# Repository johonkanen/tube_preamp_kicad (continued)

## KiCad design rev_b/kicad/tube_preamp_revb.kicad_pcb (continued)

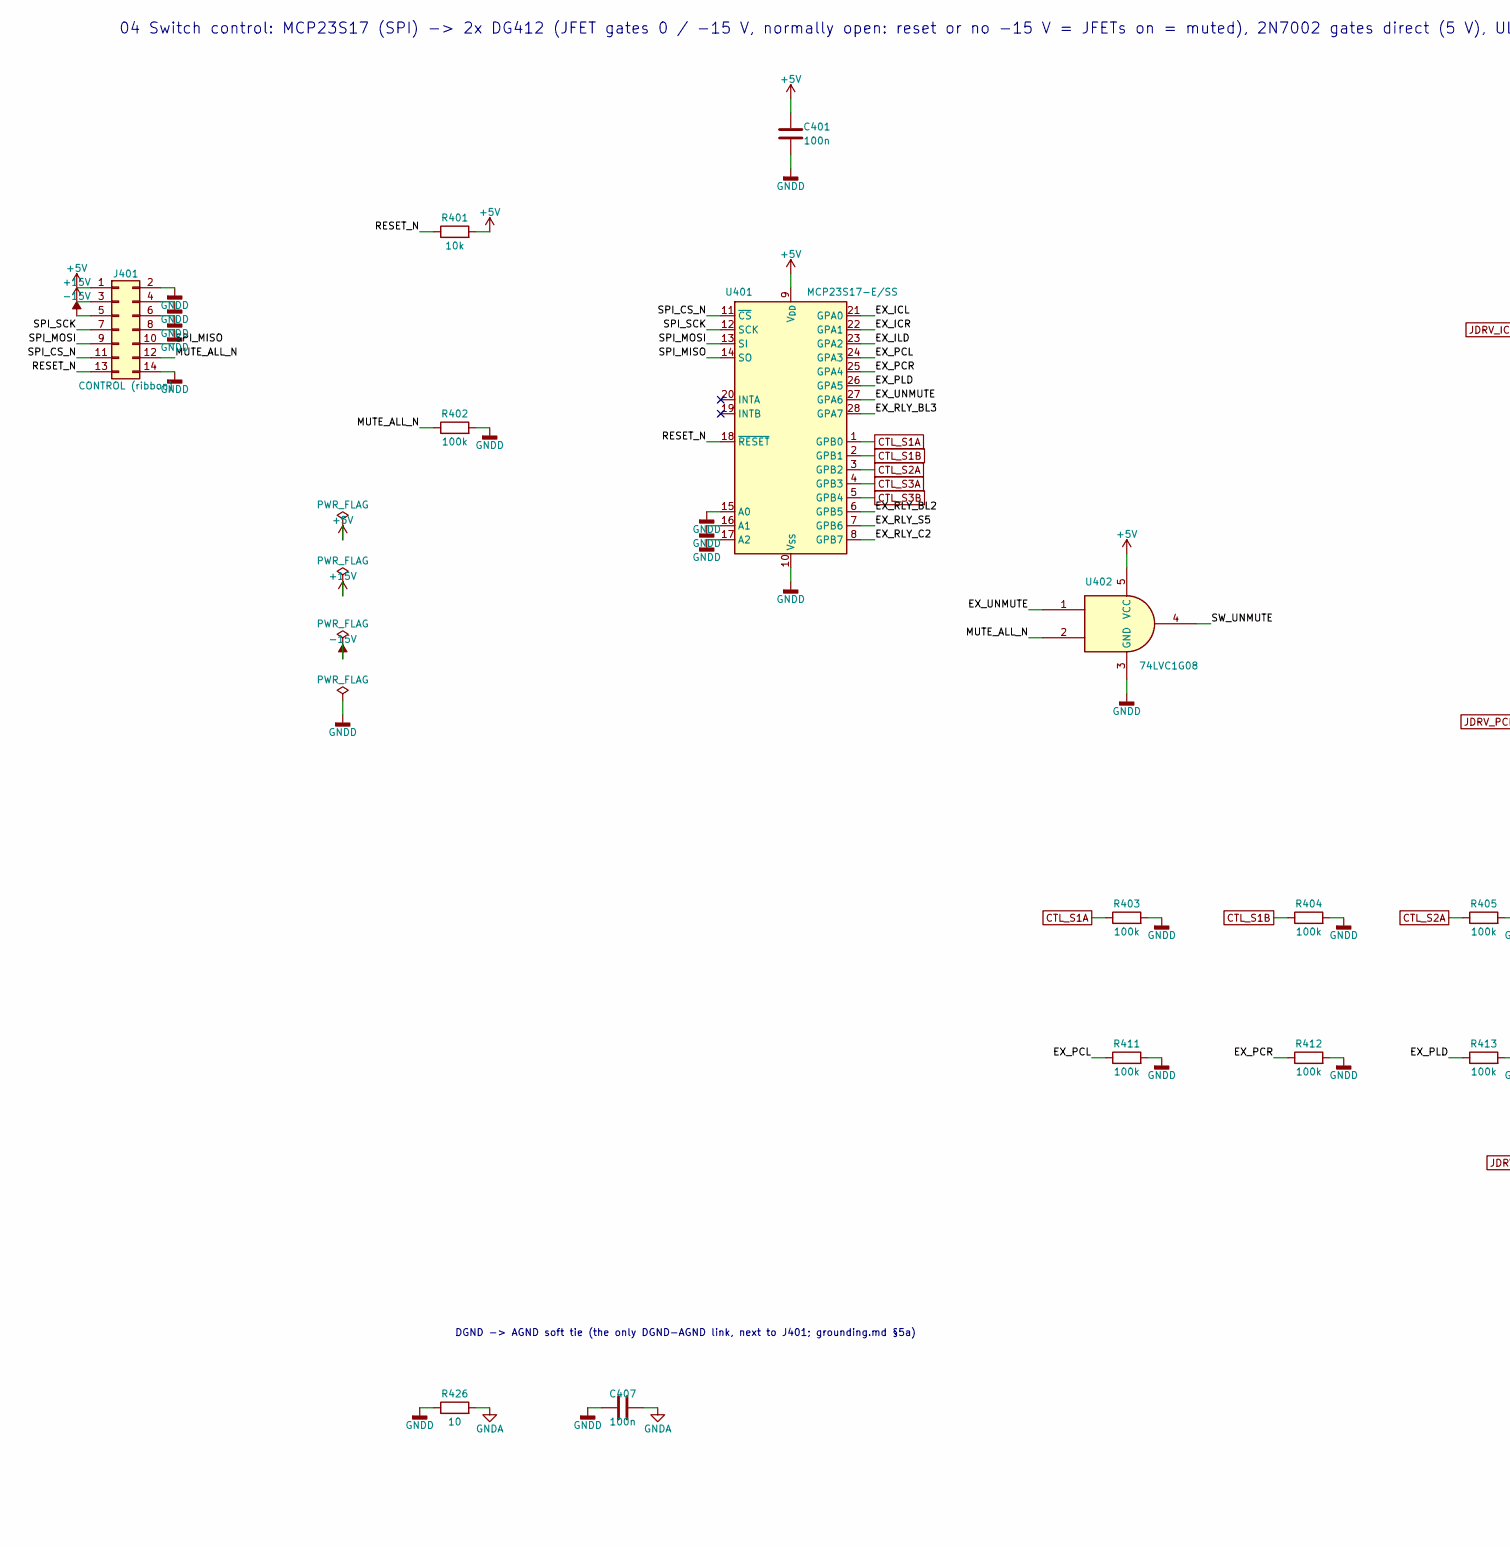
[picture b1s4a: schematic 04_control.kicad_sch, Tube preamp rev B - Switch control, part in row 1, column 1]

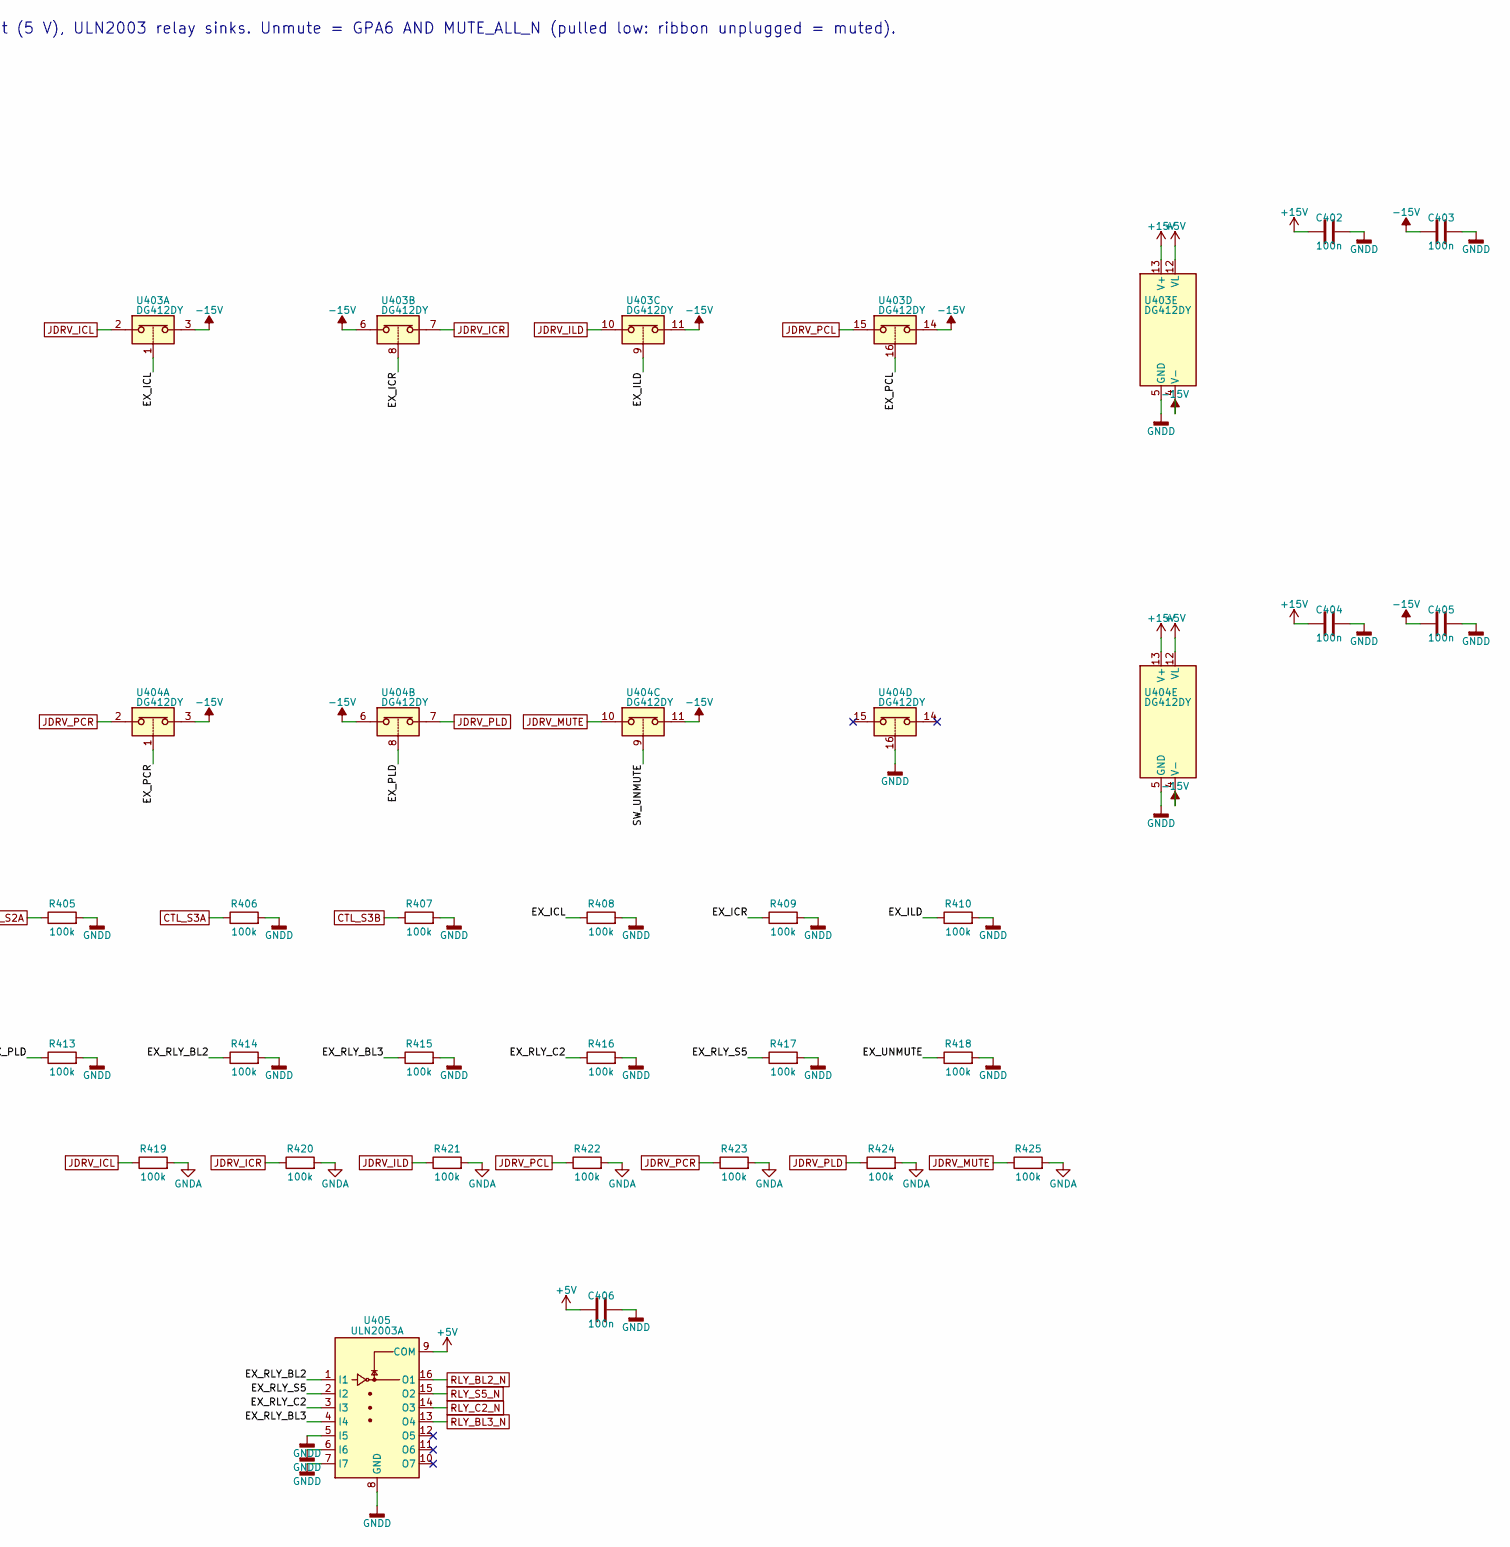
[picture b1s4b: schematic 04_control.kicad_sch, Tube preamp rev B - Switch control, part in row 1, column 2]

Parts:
C401, C402, C403, C404, C405, C406, C407: 100n; C_0603_1608Metric
J401: CONTROL (ribbon); IDC-Header_2x07_P2.54mm_Vertical
R401: 10k; R_0603_1608Metric
R402, R403, R404, R405, R406, R407, R408, R409, R410, R411, R412, R413, R414, R415, R416, R417, R418, R419, R420, R421, R422, R423, R424, R425: 100k; R_0603_1608Metric
R426: 10; R_0603_1608Metric
U401: MCP23S17-E/SS; SSOP-28_5.3x10.2mm_P0.65mm
U402: 74LVC1G08; SOT-23-5
U403, U404: DG412DY; SOIC-16_3.9x9.9mm_P1.27mm
U405: ULN2003A; SOIC-16_3.9x9.9mm_P1.27mm

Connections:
+5V: C401.1, C406.1, J401.1, R401.2, U401.9 (V_{DD}), U402.5 (VCC), U403.12 (VL), U404.12 (VL), U405.9 (COM); also elsewhere on the board
+15V: C402.1, C404.1, J401.3, U403.13 (V+), U404.13 (V+)
-15V: C403.1, C405.1, J401.5, U403.3, U403.4 (V-), U403.6, U403.11, U403.14, U404.3, U404.4 (V-), U404.6, U404.11
/04 Switch control/EX_ICL: R408.1, U401.21 (GPA0), U403.1
/04 Switch control/EX_ICR: R409.1, U401.22 (GPA1), U403.8
/04 Switch control/EX_ILD: R410.1, U401.23 (GPA2), U403.9
/04 Switch control/EX_PCL: R411.1, U401.24 (GPA3), U403.16
/04 Switch control/EX_PCR: R412.1, U401.25 (GPA4), U404.1
/04 Switch control/EX_PLD: R413.1, U401.26 (GPA5), U404.8
/04 Switch control/EX_RLY_BL2: R414.1, U401.6 (GPB5), U405.1 (I1)
/04 Switch control/EX_RLY_BL3: R415.1, U401.28 (GPA7), U405.4 (I4)
/04 Switch control/EX_RLY_C2: R416.1, U401.8 (GPB7), U405.3 (I3)
/04 Switch control/EX_RLY_S5: R417.1, U401.7 (GPB6), U405.2 (I2)
/04 Switch control/EX_UNMUTE: R418.1, U401.27 (GPA6), U402.1
/04 Switch control/MUTE_ALL_N: J401.12, R402.1, U402.2
/04 Switch control/RESET_N: J401.13, R401.1, U401.18 (~RESET)
/04 Switch control/SPI_CS_N: J401.11, U401.11 (~CS)
/04 Switch control/SPI_MISO: J401.10, U401.14 (SO)
/04 Switch control/SPI_MOSI: J401.9, U401.13 (SI)
/04 Switch control/SPI_SCK: J401.7, U401.12 (SCK)
/04 Switch control/SW_UNMUTE: U402.4, U404.9
CTL_S1A: R403.1, U401.1 (GPB0); also elsewhere on the board
CTL_S1B: R404.1, U401.2 (GPB1); also elsewhere on the board
CTL_S2A: R405.1, U401.3 (GPB2); also elsewhere on the board
CTL_S3A: R406.1, U401.4 (GPB3); also elsewhere on the board
CTL_S3B: R407.1, U401.5 (GPB4); also elsewhere on the board
GNDA: C407.2, R419.2, R420.2, R421.2, R422.2, R423.2, R424.2, R425.2, R426.2; also elsewhere on the board
GNDD: C401.2, C402.2, C403.2, C404.2, C405.2, C406.2, C407.1, J401.2, J401.4, J401.6, J401.8, J401.14, R402.2, R403.2, R404.2, R405.2, R406.2, R407.2, R408.2, R409.2, R410.2, R411.2, R412.2, R413.2, R414.2, R415.2, R416.2, R417.2, R418.2, R426.1, U401.10 (V_{SS}), U401.15 (A0), U401.16 (A1), U401.17 (A2), U402.3 (GND), U403.5 (GND), U404.5 (GND), U404.16, U405.5 (I5), U405.6 (I6), U405.7 (I7), U405.8 (GND)
JDRV_ICL: R419.1, U403.2; also elsewhere on the board
JDRV_ICR: R420.1, U403.7; also elsewhere on the board
JDRV_ILD: R421.1, U403.10; also elsewhere on the board
JDRV_MUTE: R425.1, U404.10; also elsewhere on the board
JDRV_PCL: R422.1, U403.15; also elsewhere on the board
JDRV_PCR: R423.1, U404.2; also elsewhere on the board
JDRV_PLD: R424.1, U404.7; also elsewhere on the board
RLY_BL2_N: U405.16 (O1); also elsewhere on the board
RLY_BL3_N: U405.13 (O4); also elsewhere on the board
RLY_C2_N: U405.14 (O3); also elsewhere on the board
RLY_S5_N: U405.15 (O2); also elsewhere on the board

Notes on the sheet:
04 Switch control: MCP23S17 (SPI) -> 2x DG412 (JFET gates 0 / -15 V, normally open: reset or no -15 V = JFETs on = muted), 2N7002 gates direct (5 V), ULN2003 relay sinks. Unmute = GPA6 AND MUTE_ALL_N (pulled low: ribbon unplugged = muted).
DGND -> AGND soft tie (the only DGND-AGND link, next to J401; grounding.md §5a)

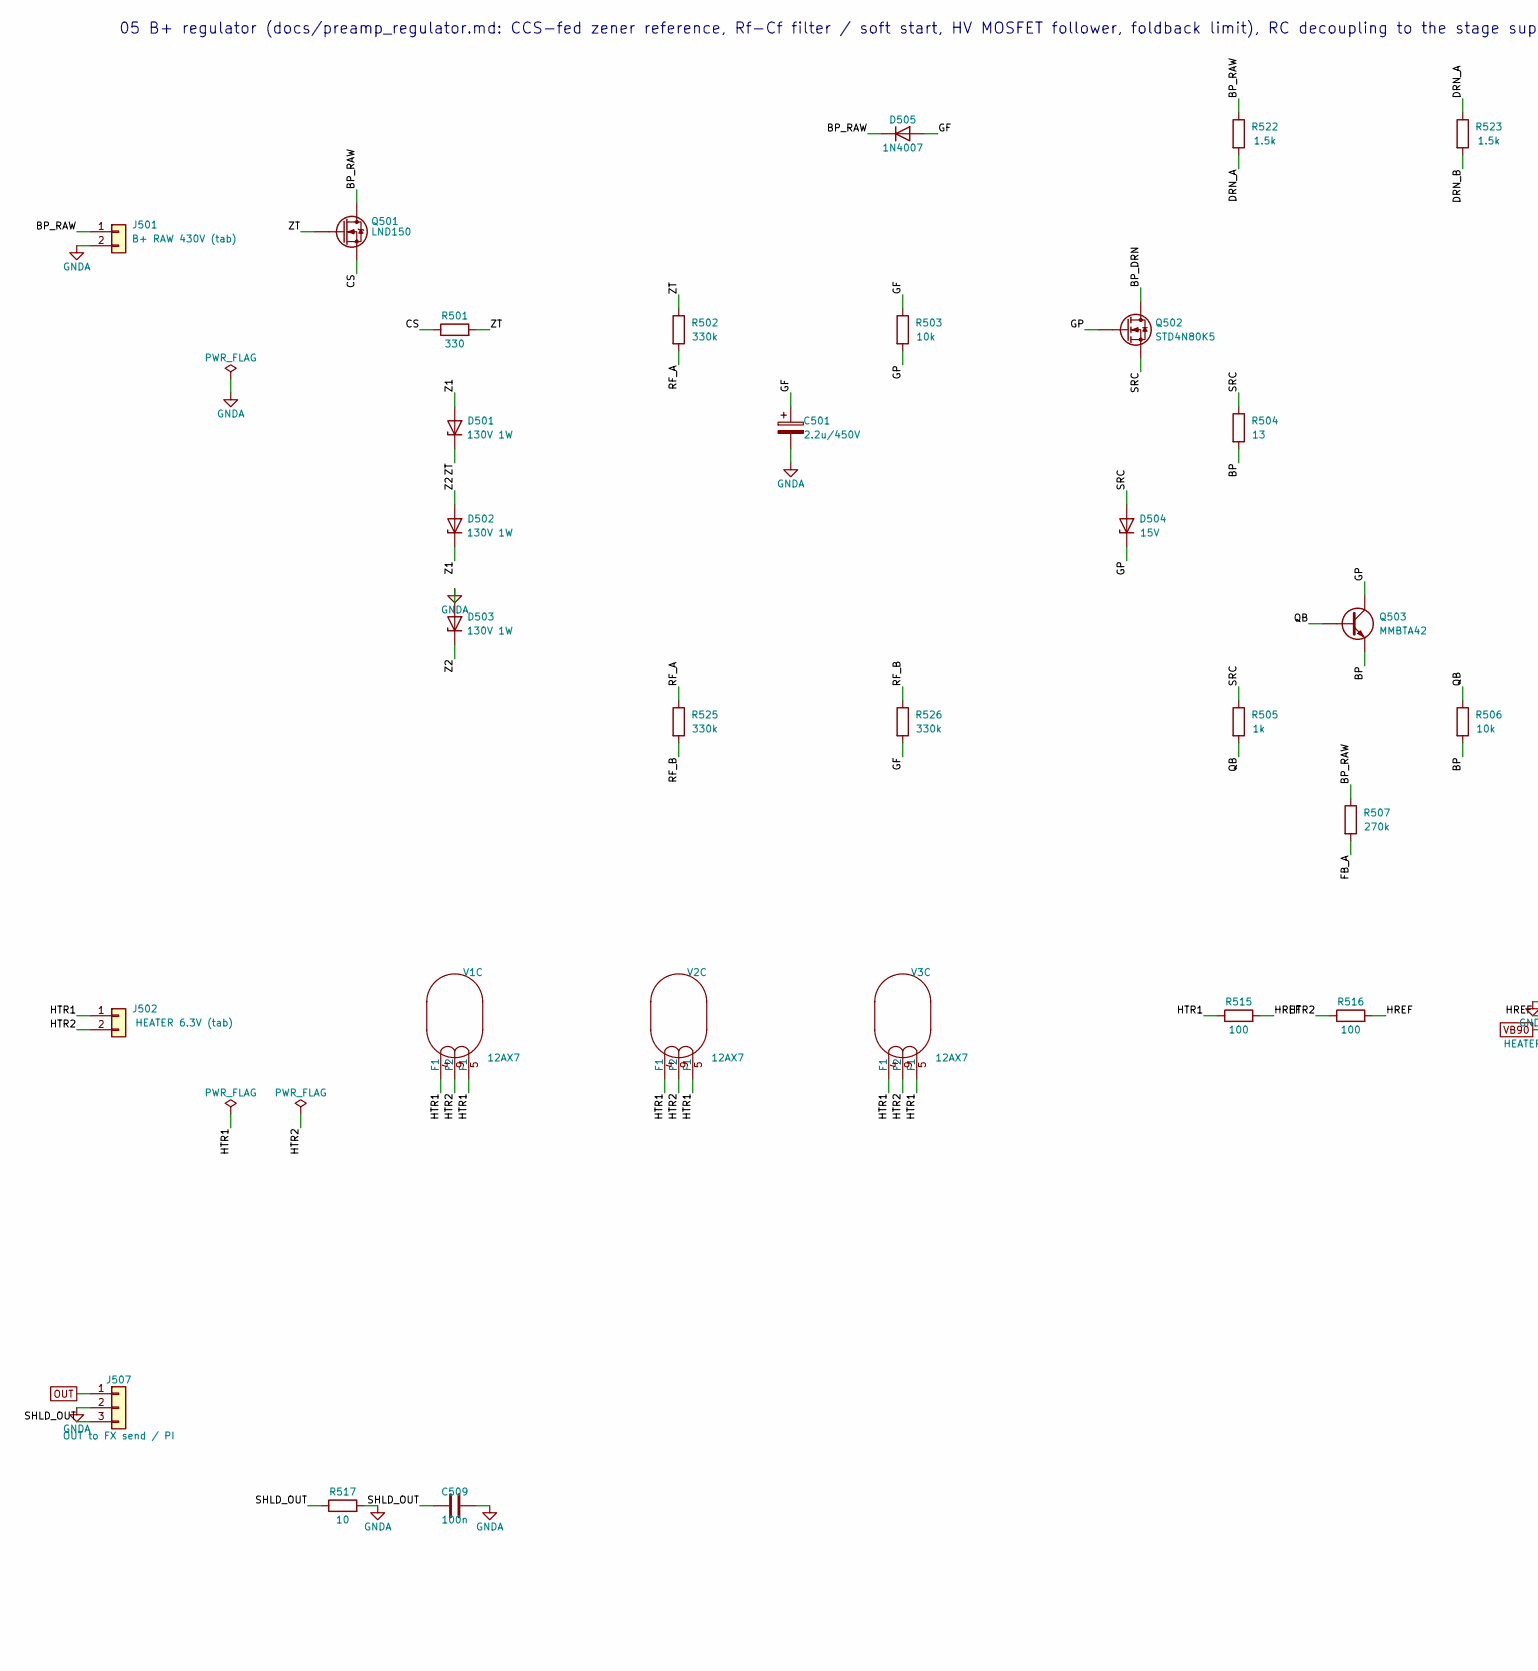
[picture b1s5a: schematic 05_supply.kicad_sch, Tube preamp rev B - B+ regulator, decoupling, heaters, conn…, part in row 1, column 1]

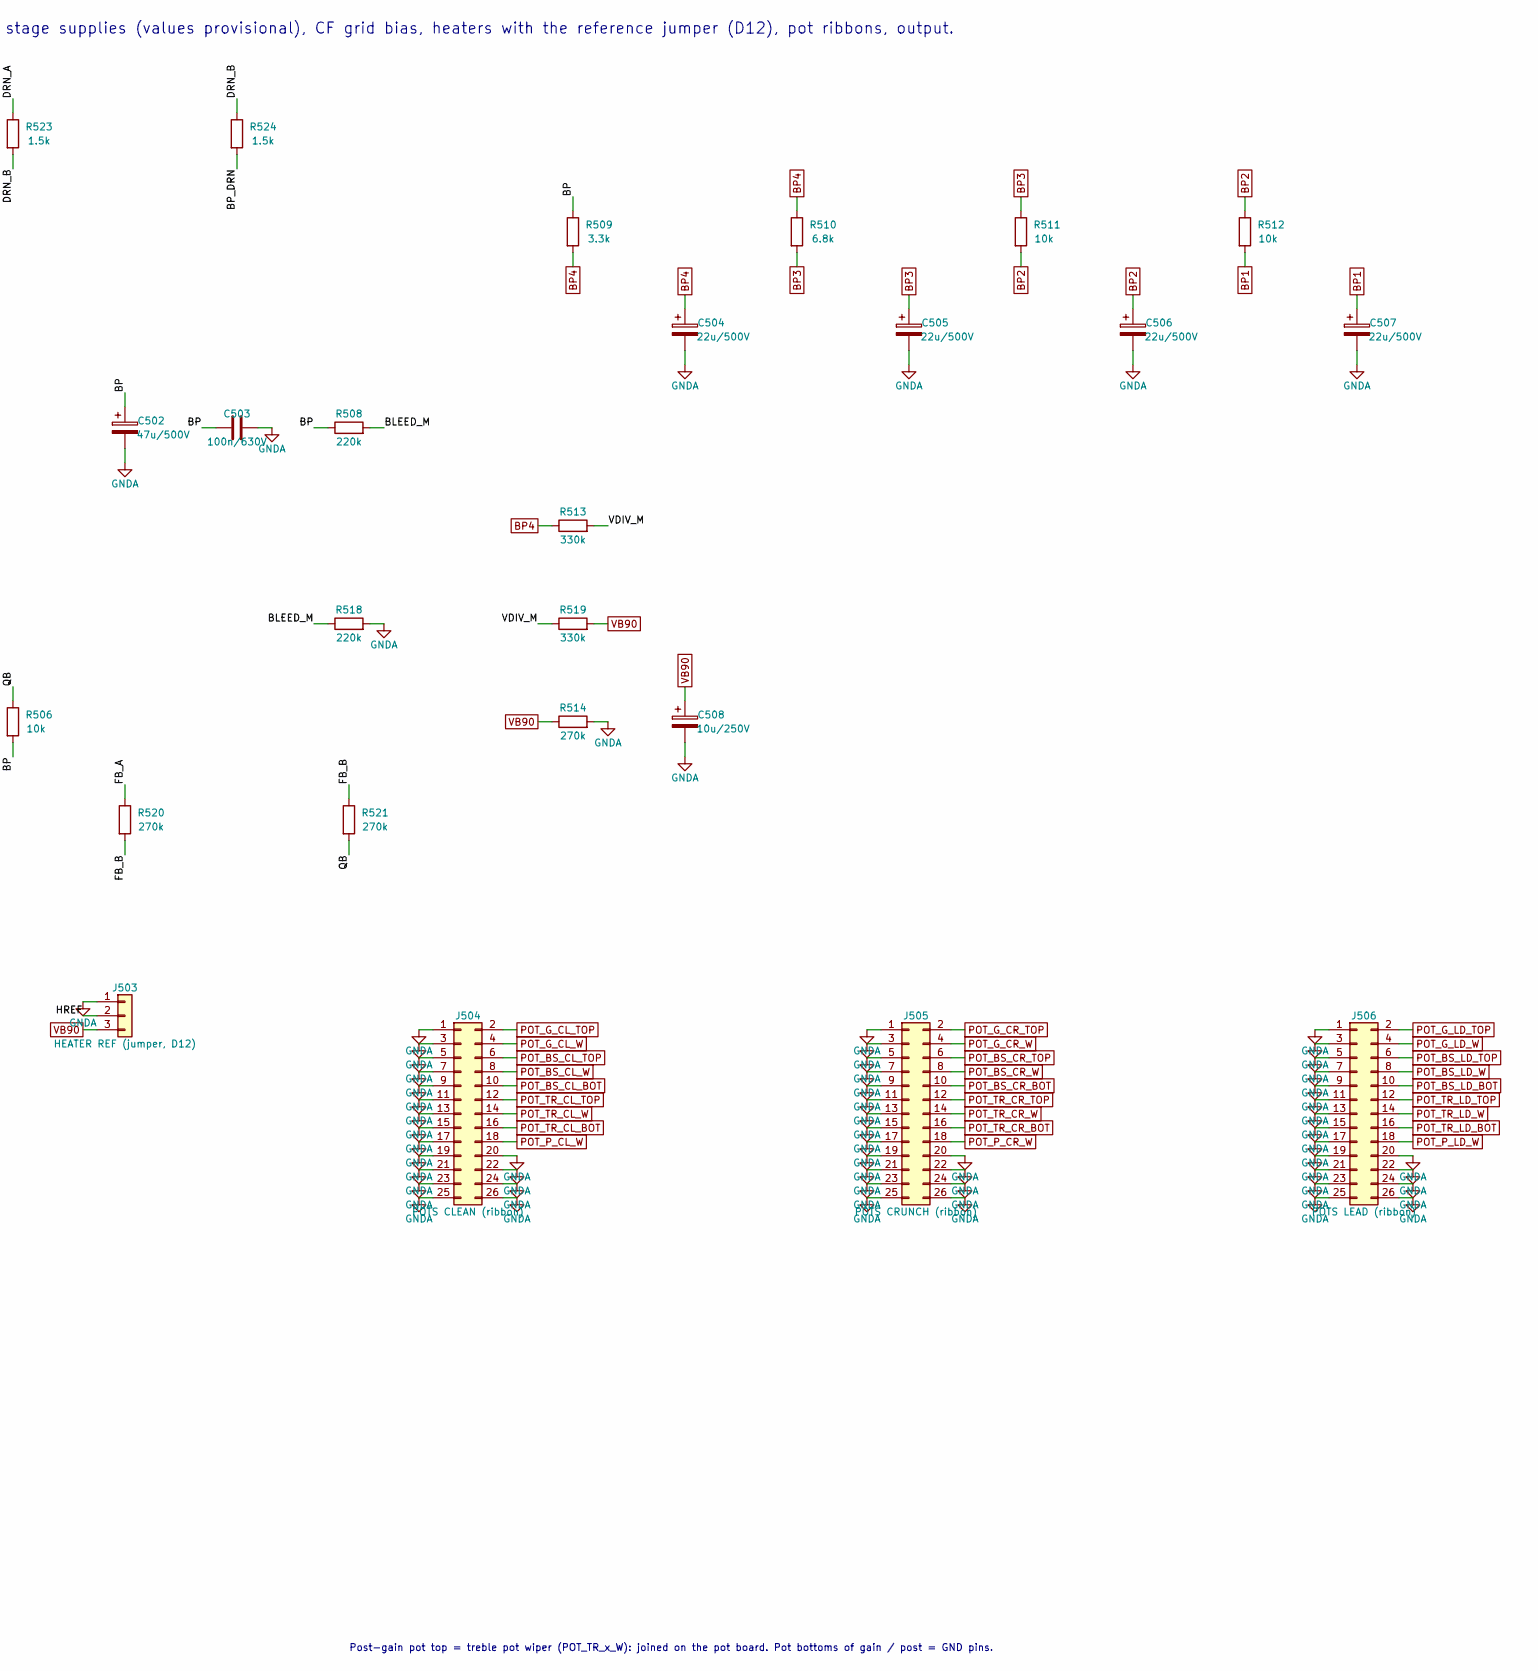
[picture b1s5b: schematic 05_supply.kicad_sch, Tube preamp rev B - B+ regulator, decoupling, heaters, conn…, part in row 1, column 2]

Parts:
C501: 2.2u/450V; CP_Radial_D8.0mm_P3.50mm
C502: 47u/500V; CP_Radial_D18.0mm_P7.50mm
C503: 100n/630V; C_Rect_L13.0mm_W6.0mm_P10.00mm_FKS3_FKP3_MKS4
C504, C505, C506, C507: 22u/500V; CP_Radial_D16.0mm_P7.50mm
C508: 10u/250V; CP_Radial_D8.0mm_P3.50mm
C509: 100n; C_0603_1608Metric
D501, D502, D503: 130V 1W; D_SMA
D504: 15V; D_SOD-123
D505: 1N4007; D_SMA
J501: B+ RAW 430V (tab); Faston_Tab_4.8mm_x2_P15.00mm
J502: HEATER 6.3V (tab); Faston_Tab_6.3mm_x2_P12.70mm
J503: HEATER REF (jumper, D12); PinHeader_1x03_P2.54mm_Vertical
J504: POTS CLEAN (ribbon); IDC-Header_2x13_P2.54mm_Vertical
J505: POTS CRUNCH (ribbon); IDC-Header_2x13_P2.54mm_Vertical
J506: POTS LEAD (ribbon); IDC-Header_2x13_P2.54mm_Vertical
J507: OUT to FX send / PI; Molex_KK-254_AE-6410-03A_1x03_P2.54mm_Vertical
Q501: LND150; SOT-89-3
Q502: STD4N80K5; TO-252-2
Q503: MMBTA42; SOT-23
R501: 330; R_1206_3216Metric
R502, R513, R519, R525, R526: 330k; R_2512_6332Metric
R503, R506: 10k; R_1206_3216Metric
R504: 13; R_1206_3216Metric
R505: 1k; R_1206_3216Metric
R507, R520, R521: 270k; R_2512_6332Metric
R508, R518: 220k; R_2512_6332Metric
R509: 3.3k; R_2512_6332Metric
R510: 6.8k; R_2512_6332Metric
R511, R512: 10k; R_2512_6332Metric
R514: 270k; R_1206_3216Metric
R515, R516: 100; R_1206_3216Metric
R517: 10; R_0603_1608Metric
R522, R523, R524: 1.5k; R_2512_6332Metric
V1, V2, V3: 12AX7; Valve_Noval_Belton_PCD21.00mm

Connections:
/05 B+ regulator, decoupling, heaters, connectors/BLEED_M: R508.2, R518.1
/05 B+ regulator, decoupling, heaters, connectors/BP: C502.1, C503.1, Q503.2 (E), R504.2, R506.2, R508.1, R509.1
/05 B+ regulator, decoupling, heaters, connectors/BP_DRN: Q502.2 (D), R524.2
/05 B+ regulator, decoupling, heaters, connectors/BP_RAW: D505.1 (K), J501.1, Q501.2 (D), R507.1, R522.1
/05 B+ regulator, decoupling, heaters, connectors/CS: Q501.3 (S), R501.1
/05 B+ regulator, decoupling, heaters, connectors/DRN_A: R522.2, R523.1
/05 B+ regulator, decoupling, heaters, connectors/DRN_B: R523.2, R524.1
/05 B+ regulator, decoupling, heaters, connectors/FB_A: R507.2, R520.1
/05 B+ regulator, decoupling, heaters, connectors/FB_B: R520.2, R521.1
/05 B+ regulator, decoupling, heaters, connectors/GF: C501.1, D505.2 (A), R503.1, R526.2
/05 B+ regulator, decoupling, heaters, connectors/GP: D504.1 (K), Q502.1 (G), Q503.3 (C), R503.2
/05 B+ regulator, decoupling, heaters, connectors/HREF: J503.2, R515.2, R516.2
/05 B+ regulator, decoupling, heaters, connectors/HTR1: J502.1, R515.1, V1.4 (F1), V1.5 (F1), V2.4 (F1), V2.5 (F1), V3.4 (F1), V3.5 (F1)
/05 B+ regulator, decoupling, heaters, connectors/HTR2: J502.2, R516.1, V1.9 (F2), V2.9 (F2), V3.9 (F2)
/05 B+ regulator, decoupling, heaters, connectors/QB: Q503.1 (B), R505.2, R506.1, R521.2
/05 B+ regulator, decoupling, heaters, connectors/RF_A: R502.2, R525.1
/05 B+ regulator, decoupling, heaters, connectors/RF_B: R525.2, R526.1
/05 B+ regulator, decoupling, heaters, connectors/SHLD_OUT: C509.1, J507.3, R517.1
/05 B+ regulator, decoupling, heaters, connectors/SRC: D504.2 (A), Q502.3 (S), R504.1, R505.1
/05 B+ regulator, decoupling, heaters, connectors/VDIV_M: R513.2, R519.1
/05 B+ regulator, decoupling, heaters, connectors/Z1: D501.2 (A), D502.1 (K)
/05 B+ regulator, decoupling, heaters, connectors/Z2: D502.2 (A), D503.1 (K)
/05 B+ regulator, decoupling, heaters, connectors/ZT: D501.1 (K), Q501.1 (G), R501.2, R502.1
BP1: C507.1, R512.2; also elsewhere on the board
BP2: C506.1, R511.2, R512.1; also elsewhere on the board
BP3: C505.1, R510.2, R511.1; also elsewhere on the board
BP4: C504.1, R509.2, R510.1, R513.1; also elsewhere on the board
GNDA: C501.2, C502.2, C503.2, C504.2, C505.2, C506.2, C507.2, C508.2, C509.2, D503.2 (A), J501.2, J503.1, J504.1, J504.3, J504.5, J504.7, J504.9, J504.11, J504.13, J504.15, J504.17, J504.19, J504.20, J504.21, J504.22, J504.23, J504.24, J504.25, J504.26, J505.1, J505.3, J505.5, J505.7, J505.9, J505.11, J505.13, J505.15, J505.17, J505.19, J505.20, J505.21, J505.22, J505.23, J505.24, J505.25, J505.26, J506.1, J506.3, J506.5, J506.7, J506.9, J506.11, J506.13, J506.15, J506.17, J506.19, J506.20, J506.21, J506.22, J506.23, J506.24, J506.25, J506.26, J507.2, R514.2, R517.2, R518.2; also elsewhere on the board
OUT: J507.1; also elsewhere on the board
POT_BS_CL_BOT: J504.10; also elsewhere on the board
POT_BS_CL_TOP: J504.6; also elsewhere on the board
POT_BS_CL_W: J504.8; also elsewhere on the board
POT_BS_CR_BOT: J505.10; also elsewhere on the board
POT_BS_CR_TOP: J505.6; also elsewhere on the board
POT_BS_CR_W: J505.8; also elsewhere on the board
POT_BS_LD_BOT: J506.10; also elsewhere on the board
POT_BS_LD_TOP: J506.6; also elsewhere on the board
POT_BS_LD_W: J506.8; also elsewhere on the board
POT_G_CL_TOP: J504.2; also elsewhere on the board
POT_G_CL_W: J504.4; also elsewhere on the board
POT_G_CR_TOP: J505.2; also elsewhere on the board
POT_G_CR_W: J505.4; also elsewhere on the board
POT_G_LD_TOP: J506.2; also elsewhere on the board
POT_G_LD_W: J506.4; also elsewhere on the board
POT_P_CL_W: J504.18; also elsewhere on the board
POT_P_CR_W: J505.18; also elsewhere on the board
POT_P_LD_W: J506.18; also elsewhere on the board
POT_TR_CL_BOT: J504.16; also elsewhere on the board
POT_TR_CL_TOP: J504.12; also elsewhere on the board
POT_TR_CL_W: J504.14; also elsewhere on the board
POT_TR_CR_BOT: J505.16; also elsewhere on the board
POT_TR_CR_TOP: J505.12; also elsewhere on the board
POT_TR_CR_W: J505.14; also elsewhere on the board
POT_TR_LD_BOT: J506.16; also elsewhere on the board
POT_TR_LD_TOP: J506.12; also elsewhere on the board
POT_TR_LD_W: J506.14; also elsewhere on the board
VB90: C508.1, J503.3, R514.1, R519.2; also elsewhere on the board

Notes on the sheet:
05 B+ regulator (docs/preamp_regulator.md: CCS-fed zener reference, Rf-Cf filter / soft start, HV MOSFET follower, foldback limit), RC decoupling to the stage supplies (values provisional), CF grid bias, heaters with the reference jumper (D12), pot ribbons, output.
Post-gain pot top = treble pot wiper (POT_TR_x_W): joined on the pot board. Pot bottoms of gain / post = GND pins.

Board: 2 copper layers, 247 parts (3 on the bottom side), 155 nets, no tracks yet.

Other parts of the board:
H101, H102, H103, H104, H105, H106, H107, H108, H109, H110, H111, H112, H113: M3 (3.2 NPTH); MountingHole_3.2mm_M3

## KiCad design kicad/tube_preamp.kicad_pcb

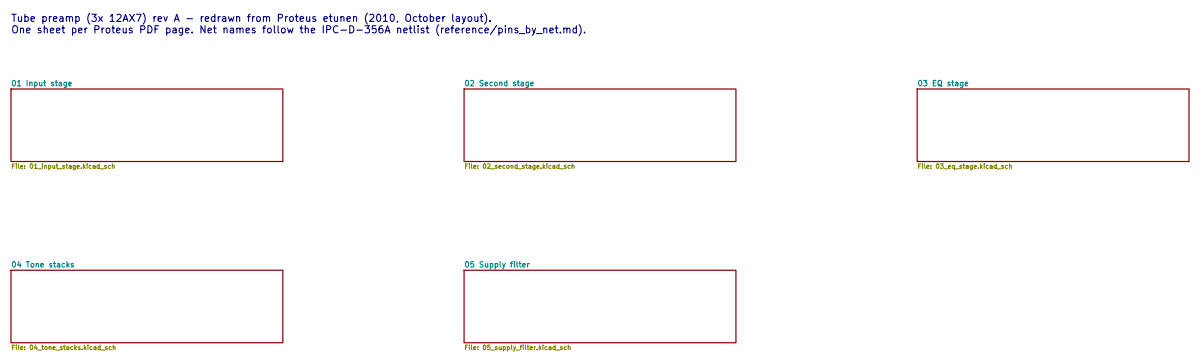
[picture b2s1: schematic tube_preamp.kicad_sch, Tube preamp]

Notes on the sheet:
Tube preamp (3x 12AX7) rev A - redrawn from Proteus etunen (2010, October layout). One sheet per Proteus PDF page. Net names follow the IPC-D-356A netlist (reference/pins_by_net.md).

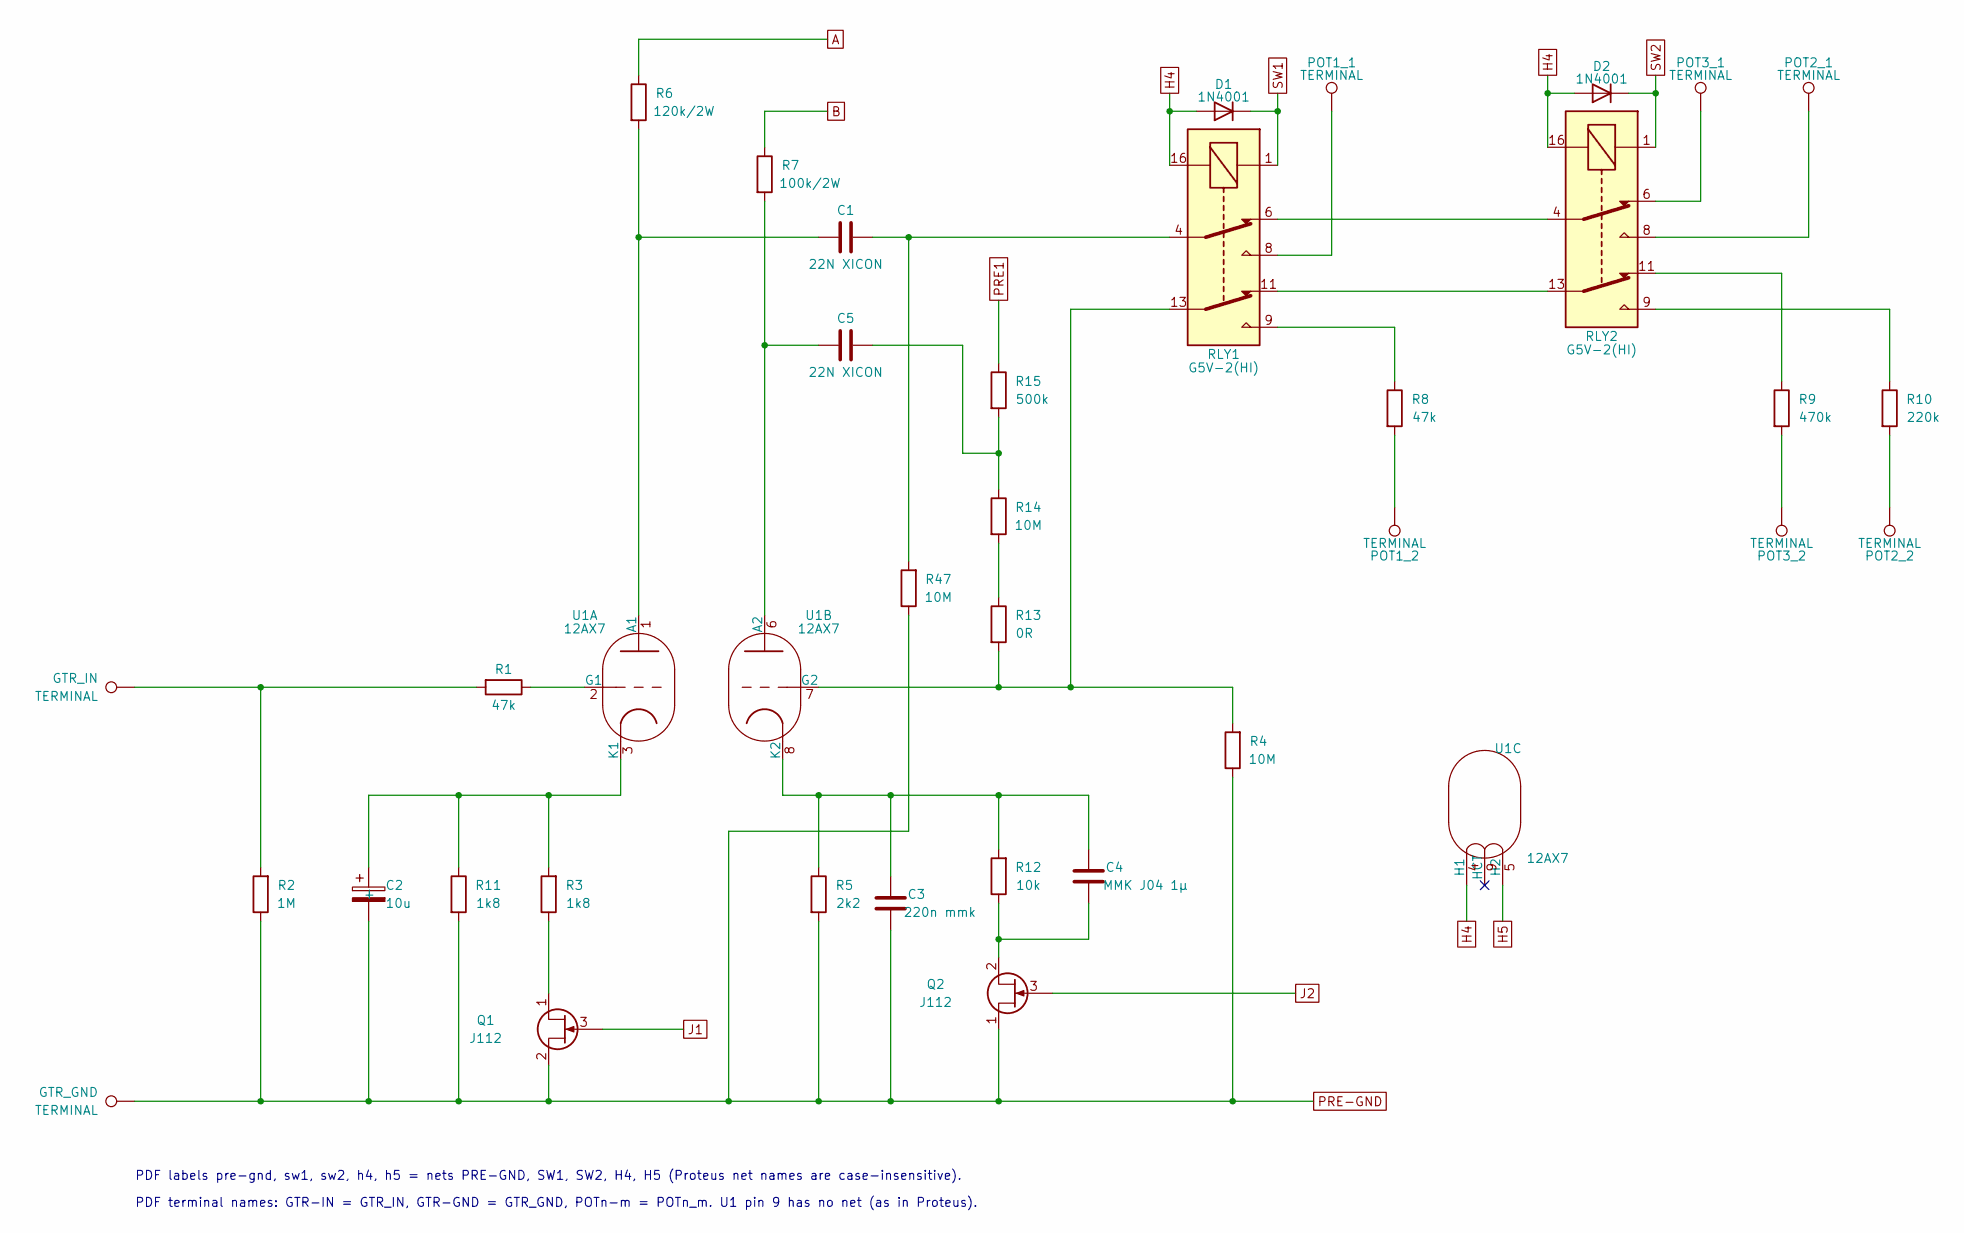
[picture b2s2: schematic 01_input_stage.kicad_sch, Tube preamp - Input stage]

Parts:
C1, C5: 22N XICON; C_Rect_L13.0mm_W6.0mm_P9.70mm
C2: 10u; CP_Radial_D6.3mm_P2.54mm_PM
C3: 220n mmk; C_Rect_L7.2mm_W2.5mm_P5.00mm_FKS2_FKP2_MKS2_MKP2
C4: MMK J04 1µ; C_Rect_L7.2mm_W5.0mm_P5.00mm
D1, D2: 1N4001; D_DO-41_SOD81_P10.16mm_Horizontal_AK
GTR_GND: TERMINAL; FlyLead_Pad_D3.048mm_Drill1.524mm
GTR_IN: TERMINAL; FlyLead_Pad_D3.048mm_Drill1.524mm
POT1_1, POT1_2, POT2_1, POT2_2, POT3_1, POT3_2: TERMINAL; FlyLead_Pad_D3.048mm_Drill1.524mm
Q1, Q2: J112; TO-92_Inline_P2.03mm
R1, R8: 47k; R_Axial_DIN0207_L6.3mm_D2.5mm_P10.16mm_Horizontal
R2: 1M; R_Axial_DIN0207_L6.3mm_D2.5mm_P10.16mm_Horizontal
R3, R11: 1k8; R_Axial_DIN0207_L6.3mm_D2.5mm_P10.16mm_Horizontal
R4, R14, R47: 10M; R_Axial_DIN0207_L6.3mm_D2.5mm_P10.16mm_Horizontal
R5: 2k2; R_Axial_DIN0207_L6.3mm_D2.5mm_P10.16mm_Horizontal
R6: 120k/2W; R_Axial_DIN0414_L11.9mm_D4.5mm_P19.05mm_Horizontal
R7: 100k/2W; R_Axial_DIN0414_L11.9mm_D4.5mm_P19.05mm_Horizontal
R9: 470k; R_Axial_DIN0207_L6.3mm_D2.5mm_P10.16mm_Horizontal
R10: 220k; R_Axial_DIN0207_L6.3mm_D2.5mm_P10.16mm_Horizontal
R12: 10k; R_Axial_DIN0207_L6.3mm_D2.5mm_P10.16mm_Horizontal
R13: 0R; R_Axial_DIN0207_L6.3mm_D2.5mm_P10.16mm_Horizontal
R15: 500k; R_Axial_DIN0207_L6.3mm_D2.5mm_P10.16mm_Horizontal
RLY1, RLY2: G5V-2(HI); Relay_DPDT_Omron_G5V-2
U1: 12AX7; Valve_Noval_Belton_PCD21.00mm

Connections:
A: R6.1; also elsewhere on the board
B: R7.1; also elsewhere on the board
H4: D1.A, D2.A, RLY1.16, RLY2.16, U1.4 (H1); also elsewhere on the board
H5: U1.5 (H2); also elsewhere on the board
J1: Q1.3 (G); also elsewhere on the board
J2: Q2.3 (G); also elsewhere on the board
unnamed: C1.2, R47.2, RLY1.4
unnamed: C5.2, R14.1, R15.2
unnamed: GTR_IN.1, R1.2, R2.2
unnamed: POT1_1.1, RLY1.8
unnamed: POT1_2.1, R8.2
unnamed: POT2_1.1, RLY2.8
unnamed: POT2_2.1, R10.2
unnamed: POT3_1.1, RLY2.6
unnamed: POT3_2.1, R9.2
unnamed: Q1.1 (D), R3.1
unnamed: C4.2, Q2.2 (S), R12.1
unnamed: R8.1, RLY1.9
unnamed: R9.1, RLY2.11
unnamed: R10.1, RLY2.9
unnamed: R13.1, R14.2
unnamed: RLY1.6, RLY2.4
unnamed: RLY1.11, RLY2.13
unnamed: C1.1, R6.2, U1.1 (A1)
unnamed: R1.1, U1.2 (G1)
unnamed: C2.+, R3.2, R11.1, U1.3 (K1)
unnamed: C5.1, R7.2, U1.6 (A2)
unnamed: R4.2, R13.2, RLY1.13, U1.7 (G2)
unnamed: C3.2, C4.1, R5.1, R12.2, U1.8 (K2)
PRE1: R15.1; also elsewhere on the board
PRE-GND: C2.-, C3.1, GTR_GND.1, Q1.2 (S), Q2.1 (D), R2.1, R4.1, R5.2, R11.2, R47.1; also elsewhere on the board
SW1: D1.K, RLY1.1; also elsewhere on the board
SW2: D2.K, RLY2.1; also elsewhere on the board

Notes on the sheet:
PDF labels pre-gnd, sw1, sw2, h4, h5 = nets PRE-GND, SW1, SW2, H4, H5 (Proteus net names are case-insensitive).
PDF terminal names: GTR-IN = GTR_IN, GTR-GND = GTR_GND, POTn-m = POTn_m. U1 pin 9 has no net (as in Proteus).
